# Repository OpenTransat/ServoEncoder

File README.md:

# ServoEncoder
Controls a motor by evaluating position feedback from a magnetic encoder

## Features

* Based on Atmega328P @ 2 MHz

* Absolute magnetic rotary encoder EMS22A is mounted on the PCB

* Used with JGY-2838 or a similar motor controlled by a two-wire interface

* The two-wire output can be used as serial RX/TX for debugging

* One can use a stepper motor by connecting the two-wire output to a stepper motor driver

* PWM input like a typical servo or serial input (serial version has been chosen as it's more precise than reading the pulse length)

* It provides a feedback to the main controller to determine if the motor is overloaded or stuck

It has been designed as a robust solution for steering the rudder on autonomous boat. The life span has been tested with a worm geared motor JGY-2838.

Ongoing test: 2 million cycles

## Video: Testing worm drive life span

## Video: The actual application

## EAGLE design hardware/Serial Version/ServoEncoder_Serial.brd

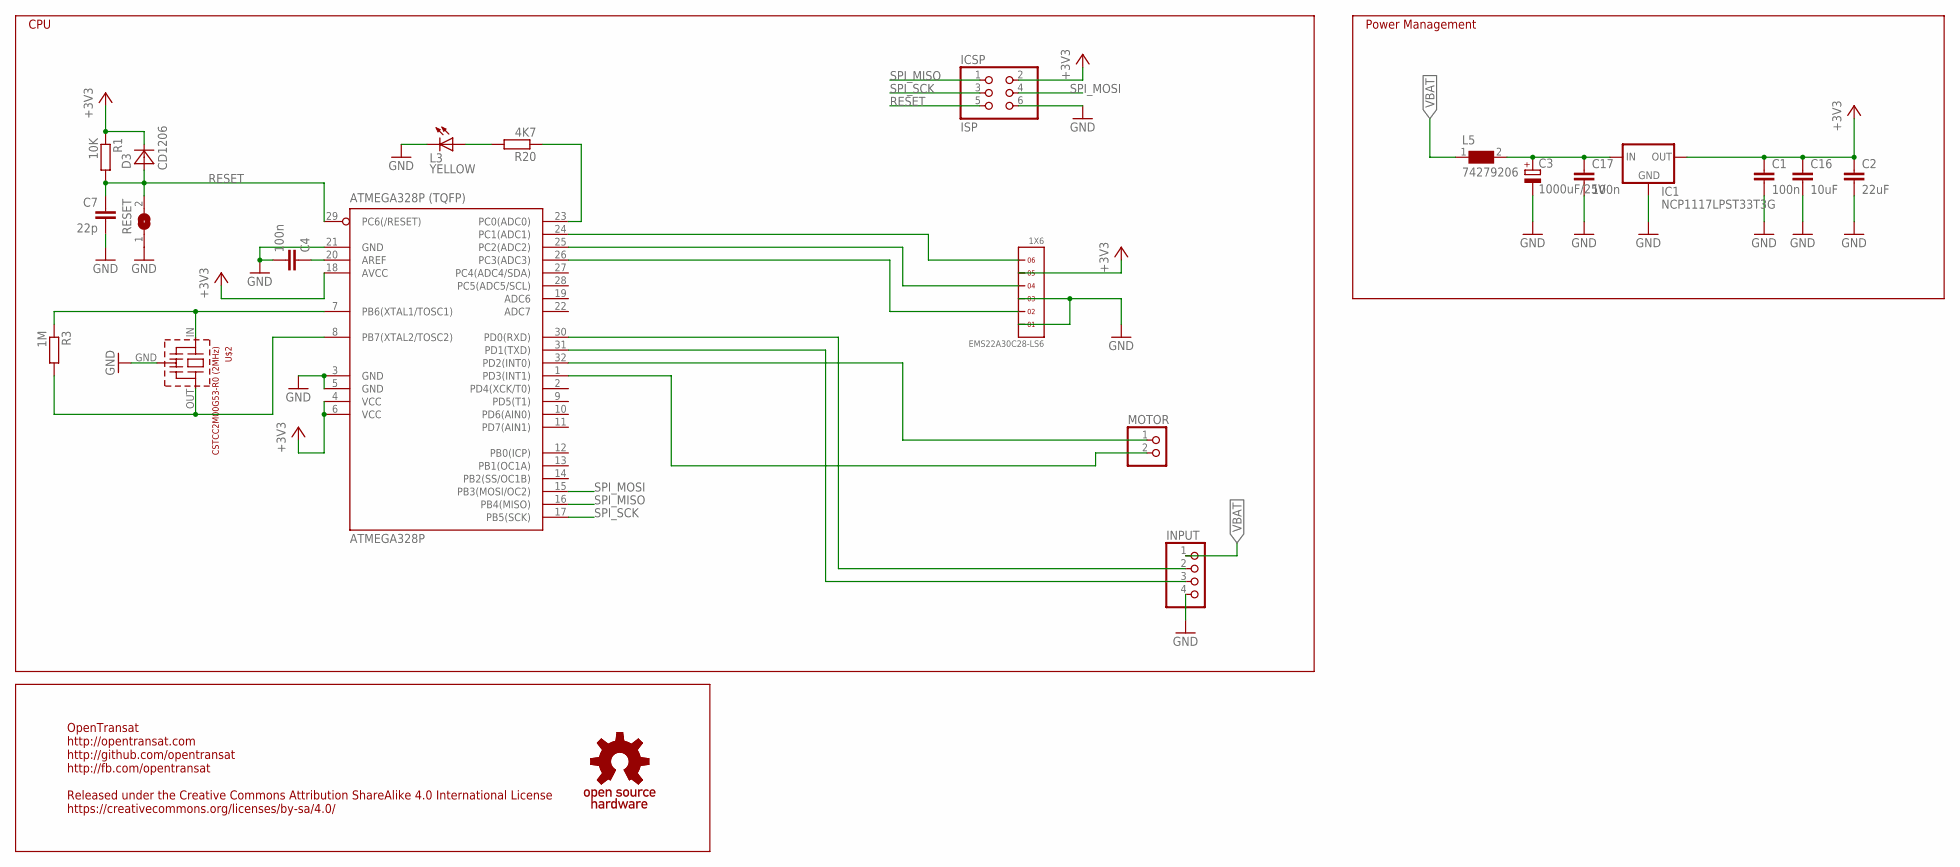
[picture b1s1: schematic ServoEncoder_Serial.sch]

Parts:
ATMEGA328P: ATMEGA328P (TQFP); TQFP32-08
C1, C4, C17: 100n; C0603
C2: 22uF; C1210
C3: 1000uF/25V; E5-10,5
C7: 22p; C0603
C16: 10uF; C1206
D3: CD1206; R1206
EMS22A30C28-LS6: 1X6
IC1: NCP1117LPST33T3G; SOT223
ICSP: ISP; 2X03
INPUT: PINHD-1X4; 1X04
L3: YELLOW; CHIPLED_0805
L5: 74279206; 0805
MOTOR: PINHD-1X2; 1X02
R1: 10K; R0603
R3: 1M; R0603
R20: 4K7; R0603
RESET: SJW
U$1: OSHW_S; OSHWS
U$2: CSTCC2M00G53-R0 (2MHz); CSTCC

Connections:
+3V3: ATMEGA328P.4 (VCC), ATMEGA328P.6 (VCC), ATMEGA328P.18 (AVCC), C1.1, C2.1, C16.1, D3.2 (C), EMS22A30C28-LS6.5, IC1.2 (OUT), IC1.4 (OUT), ICSP.2, R1.1
AREF: ATMEGA328P.20 (AREF), C4.1
GND: ATMEGA328P.3 (GND), ATMEGA328P.5 (GND), ATMEGA328P.21 (GND), C1.2, C2.2, C3.-, C4.2, C7.2, C16.2, C17.2, EMS22A30C28-LS6.1, EMS22A30C28-LS6.3, IC1.1 (GND), ICSP.6, INPUT.4, L3.C, RESET.1, U$2.GND
L13: ATMEGA328P.23 (PC0(ADC0)), R20.1
unnamed: C3.+, C17.1, IC1.3 (IN), L5.2
unnamed: ATMEGA328P.30 (PD0(RXD)), INPUT.2
unnamed: L3.A, R20.2
unnamed: ATMEGA328P.31 (PD1(TXD)), INPUT.3
unnamed: ATMEGA328P.1 (PD3(INT1)), MOTOR.2
unnamed: ATMEGA328P.24 (PC1(ADC1)), EMS22A30C28-LS6.6
unnamed: ATMEGA328P.25 (PC2(ADC2)), EMS22A30C28-LS6.4
unnamed: ATMEGA328P.26 (PC3(ADC3)), EMS22A30C28-LS6.2
unnamed: ATMEGA328P.32 (PD2(INT0)), MOTOR.1
RESET: ATMEGA328P.29 (PC6(/RESET)), C7.1, D3.1 (A), ICSP.5, R1.2, RESET.2
SPI_MISO: ATMEGA328P.16 (PB4(MISO)), ICSP.1
SPI_MOSI: ATMEGA328P.15 (PB3(MOSI/OC2)), ICSP.4
SPI_SCK: ATMEGA328P.17 (PB5(SCK)), ICSP.3
VBAT: INPUT.1, L5.1
XTAL1: ATMEGA328P.8 (PB7(XTAL2/TOSC2)), R3.2, U$2.OUT
XTAL2: ATMEGA328P.7 (PB6(XTAL1/TOSC1)), R3.1, U$2.IN

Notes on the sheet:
OpenTransat http://opentransat.com http://github.com/opentransat http://fb.com/opentransat Released under the Creative Commons Attribution ShareAlike 4.0 International License https://creativecommons.org/licenses/by-sa/4.0/
Power Management
CPU

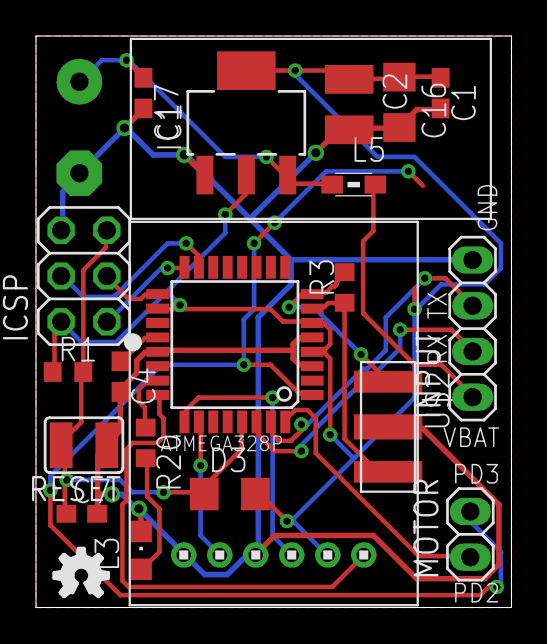
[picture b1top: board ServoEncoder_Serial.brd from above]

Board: 2 copper layers, 26.4 x 31.8 mm, 22 parts (1 on the bottom side), 20 nets.

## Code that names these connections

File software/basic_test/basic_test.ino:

/*
ServoEncoder
TEST PROGRAM

https://github.com/OpenTransat/ServoEncoder

Released under the Creative Commons Attribution ShareAlike 4.0 International License
https://creativecommons.org/licenses/by-sa/4.0/
*/

#define SERIAL_DEBUG //switch between serial debug and motor
#define LED 14 //PC0
#define PIN_CS 15 //PC1, EMS:6
#define PIN_CLK 17 //PC3, EMS:2
#define PIN_DO 16 //PC2, EMS:4
#define PIN_ON 0 //PD0
#define PIN_REV 1 //PD1
#define PIN_PWM 2 //PD2
#define PIN_FB 3 //PD3
#define ZERO_POS 30
#define DELTA 70

void setup() {
  pinMode(LED, OUTPUT);

  pinMode(PIN_CS, OUTPUT);
  digitalWrite(PIN_CS, HIGH);
  pinMode(PIN_CLK, OUTPUT);
  digitalWrite(PIN_CLK, HIGH);
  pinMode(PIN_DO, INPUT);

  #ifdef SERIAL_DEBUG
    Serial.begin(9600); //9600 supported for 2MHz
  #else
    pinMode(PIN_ON, OUTPUT);
    digitalWrite(PIN_ON, HIGH);
    pinMode(PIN_REV, OUTPUT);
    digitalWrite(PIN_REV, HIGH);
  #endif
}

byte dir = 1;

void gotopos(int where, int where_stop) {
  digitalWrite(PIN_CS, LOW);
  delayMicroseconds(1);  
  byte b[16];
  int pos = 0;
  byte parity = 0;

  for (int i = 0; i < 16; i++) {
    digitalWrite(PIN_CLK, LOW);
    delayMicroseconds(1);
    digitalWrite(PIN_CLK, HIGH);
    b[i] = digitalRead(PIN_DO) == HIGH ? 1 : 0;

    if (i < 15)
      parity += b[i];
  }

  parity %= 2;

  if (b[15] == parity) {

    for (int i = 0; i < 10; i++) {
      pos += b[i] * (1 << 10-(i+1));
    }

    pos = (pos - ZERO_POS) % 1024;
    if (pos > 512)
      pos = pos - 1024;

    if (pos < where && pos < where_stop) {
      #ifdef SERIAL_DEBUG
        Serial.println("go forward");
      #else
        digitalWrite(PIN_ON, LOW);
        digitalWrite(PIN_REV, LOW);
      #endif
    } else if (pos > where && pos > where_stop) {
      #ifdef SERIAL_DEBUG
        Serial.println("go back");
      #else
        digitalWrite(PIN_ON, LOW);
        digitalWrite(PIN_REV, HIGH);
      #endif
    }
    else if (pos > where && pos < where_stop) {
      #ifdef SERIAL_DEBUG
      #else
        digitalWrite(PIN_ON, HIGH);      
      #endif
    }
    else if (pos < where && pos > where_stop) {
      #ifdef SERIAL_DEBUG
      #else
        digitalWrite(PIN_ON, HIGH);      
      #endif
    }
  
    #ifdef SERIAL_DEBUG
      Serial.println(pos);
    #endif
  }
  else {
    digitalWrite(PIN_CS, HIGH);
    #ifdef SERIAL_DEBUG
      Serial.println("parity error!");
    #else
      digitalWrite(PIN_ON, HIGH);
      digitalWrite(PIN_REV, HIGH);
    #endif
    delay(1000);
  }
  digitalWrite(PIN_CS, HIGH);
}

unsigned long previousMillis = 0;
#define INTERVAL 1000UL
byte state = 0;

void loop() {
  unsigned long currentMillis = millis();

  if (currentMillis < previousMillis) { //millis() overflow
    previousMillis = 0;
  }
  
  if (currentMillis - previousMillis >= INTERVAL) {
    previousMillis = currentMillis;
    state = 1 - state;
  }

  if (state)
    gotopos(DELTA, DELTA+50);
  else
    gotopos(-DELTA, -DELTA-50);
}

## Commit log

2018-05-07 Rename hardware/ServoEncoder.sch to hardware/PWM Version/ServoEncoder.sch
2018-05-07 Rename hardware/ServoEncoder.brd to hardware/PWM Version/ServoEncoder.brd
2018-05-07 Rename software/ServoEncoder.ino to software/PWM Version/ServoEncoder.ino
2018-05-07 Rename software/ServoEncoder_Serial.ino to software/Serial Version/ServoEncoder_Serial.ino

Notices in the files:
parts and their libraries:
Wurth_Elektronik_Passive_rev15b: Copyright: Würth Elektronik
